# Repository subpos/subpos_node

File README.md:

# SubPos Node Gerber Files and Firmware

The latest firmware should be used with the latest version of the ESP firmware, available here - https://github.com/subpos/esp_firmware_v2

You can order 3 of these boards for $7.5 including shipping from OSHPark here - https://oshpark.com/shared_projects/0TVEe4yb

Note, the current Node design will not support Time of Flight. Because of this, there is no need to populate QG1 as the firmware just uses the internal PIC oscillator.

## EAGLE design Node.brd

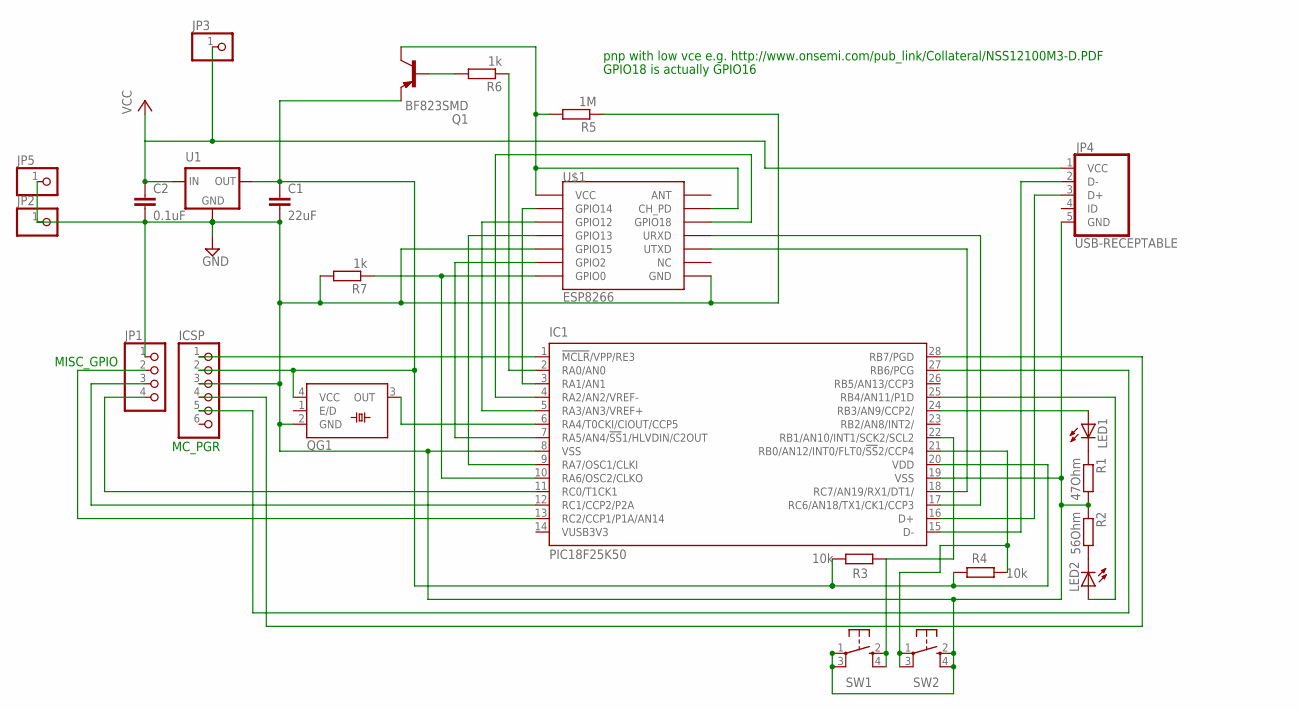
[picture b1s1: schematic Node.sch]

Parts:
C1: 22uF; C0805
C2: 0.1uF; C0805
IC1: PIC18F25K50; SO28W
ICSP: PINHD-1X6; 1X06
JP1: PINHD-1X4; 1X04
JP2, JP3, JP5: PINHD-1X1; 1X01
JP4: USB-RECEPTABLE; FCI-10103594-0001LF
LED1, LED2: LEDCHIPLED_0805; CHIPLED_0805
Q1: BF823SMD; SOT23-BEC
QG1: SM77H
R1: 47Ohm; M0805
R2: 56Ohm; M0805
R3, R4: 10k; M0805
R5: 1M; M0805
R6, R7: 1k; M0805
SW1, SW2: SPST_TACT-KMR2; KMR2
U1: MIC5209-X.XYS; SOT223
U$1: ESP8266; ESP-03

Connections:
GND: C1.2, C2.2, IC1.8 (VSS), IC1.19 (VSS), ICSP.3, JP1.1, JP2.1, JP4.5 (GND), JP5.1, QG1.2 (GND), R1.2, R2.1, R5.1, R7.2, SW1.1, SW1.3 (P1), SW2.2 (S), SW2.4 (S1), U1.2 (GND), U1.4 (GND), U$1.GND, U$1.GPIO15
unnamed: IC1.28 (RB7/PGD), ICSP.4
unnamed: C1.1, IC1.20 (VDD), ICSP.2, Q1.E, QG1.4 (VCC), R3.1, R4.2, U1.3 (OUT)
unnamed: IC1.27 (RB6/PCG), ICSP.5
unnamed: IC1.2 (RA0/AN0), R6.1
unnamed: IC1.17 (RC6/AN18/TX1/CK1/CCP3), U$1.URXD
unnamed: IC1.18 (RC7/AN19/RX1/DT1/), U$1.UTXD
unnamed: IC1.1 (!MCLR!/VPP/RE3), ICSP.1
unnamed: IC1.3 (RA1/AN1), U$1.GPIO14
unnamed: IC1.5 (RA3/AN3/VREF+), U$1.GPIO12
unnamed: IC1.16 (D+), JP4.3 (D+)
unnamed: IC1.15 (D-), JP4.2 (D-)
unnamed: LED1.C, R1.1
unnamed: IC1.24 (RB3/AN9/CCP2/), LED1.A
unnamed: LED2.C, R2.2
unnamed: IC1.25 (RB4/AN11/P1D), LED2.A
unnamed: IC1.11 (RC0/T1CK1), JP1.4
unnamed: IC1.13 (RC2/CCP1/P1A/AN14), JP1.2
unnamed: IC1.9 (RA7/OSC1/CLKI), U$1.GPIO13
unnamed: IC1.6 (RA4/T0CKI/CIOUT/CCP5), QG1.3 (OUT)
unnamed: IC1.12 (RC1/CCP2/P2A), JP1.3
unnamed: IC1.7 (RA5/AN4/!SS!1/HLVDIN/C2OUT), U$1.GPIO2
unnamed: IC1.4 (RA2/AN2/VREF-), U$1.GPIO18
unnamed: IC1.10 (RA6/OSC2/CLKO), R7.1, U$1.GPIO0
unnamed: IC1.22 (RB1/AN10/INT1/SCK2/SCL2), R3.2, SW1.2 (S), SW1.4 (S1)
unnamed: IC1.21 (RB0/AN12/INT0/FLT0/!SS!2/CCP4), R4.1, SW2.1, SW2.3 (P1)
unnamed: Q1.B, R6.2
unnamed: Q1.C, R5.2, U$1.CH_PD, U$1.VCC
VCC: C2.1, JP3.1, JP4.1 (VCC), U1.1 (IN)

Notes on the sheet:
MC_PGR
MISC_GPIO
GPIO18 is actually GPIO16
pnp with low vce e.g. http://www.onsemi.com/pub_link/Collateral/NSS12100M3-D.PDF

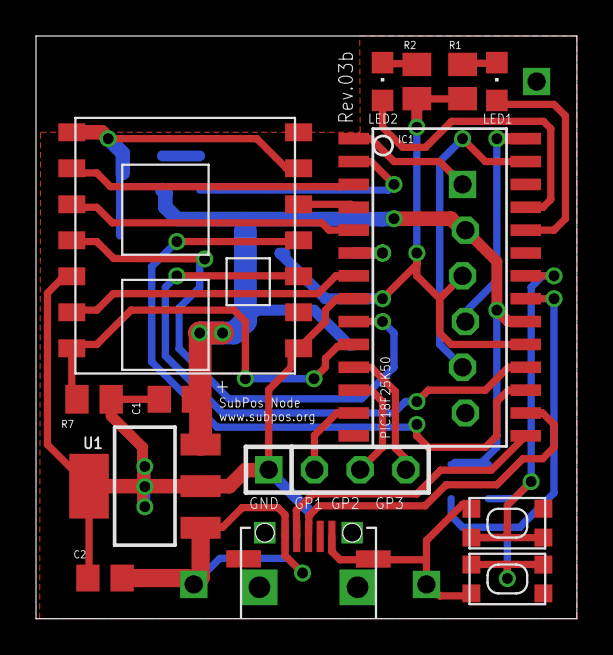
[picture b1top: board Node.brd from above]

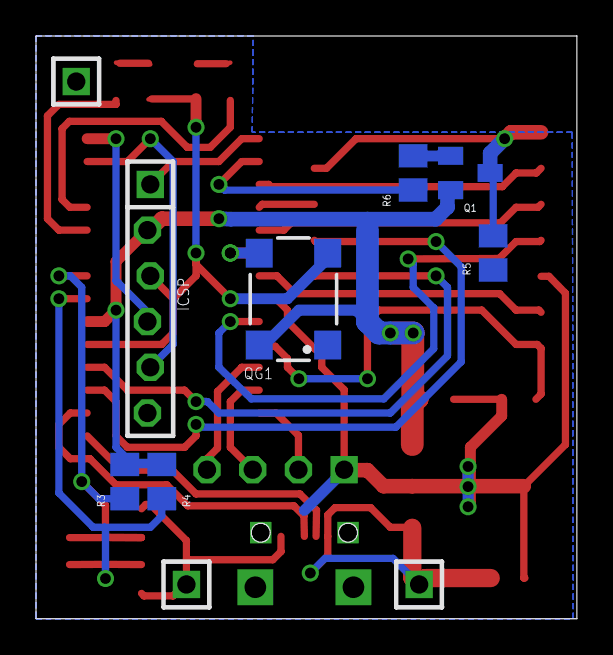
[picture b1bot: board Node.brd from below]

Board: 2 copper layers, 30.0 x 32.4 mm, 24 parts (9 on the bottom side), 29 nets.

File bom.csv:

Part;Value;Device;Package;Description
C1;22µF Tantalum 4V;C-EUC0805;C0805;CAPACITOR, European symbol
C2;0.1µF Ceramic 25V ;C-EUC0805;C0805;CAPACITOR, European symbol
IC1;PIC18F25K50;PIC18F25K50-I/SO;SO28W;PIC18F25K50 28 pin DIP
ICSP;2.54mm;PINHD-1X6;1X06;PIN HEADER
JP1;2.54mm;PINHD-1X4;1X04;PIN HEADER
JP2;;FCI-10103594-0001LF;USB-RECEPTABLE;USB Receptable
LED1;RED 22MCD;KPT-2012LSURCK;CHIPLED_0805;LED
LED2;GREEN 3MCD;KPT-2012LCGCK;CHIPLED_0805;LED
Q1;PNP Low Vce;NSV40200LT1G ;SOT23-BEC;PNP Transistror
R1;47Ohm;R-EU_M0805;M0805;RESISTOR, European symbol
R2;56Ohm;R-EU_M0805;M0805;RESISTOR, European symbol
R3;10k;R-EU_M0805;M0805;RESISTOR, European symbol
R4;10k;R-EU_M0805;M0805;RESISTOR, European symbol
R5;1M;R-EU_M0805;M0805;RESISTOR, European symbol
R6;1k;R-EU_M0805;M0805;RESISTOR, European symbol
R7;1k;R-EU_M0805;M0805;RESISTOR, European symbol
SW1;SPST_TACT-KMR2;SPST_TACT-KMR2;KMR2;SMT 6mm switch, EVQQ2 series
SW2;SPST_TACT-KMR2;SPST_TACT-KMR2;KMR2;SMT 6mm switch, EVQQ2 series
U1;MIC5209-X.XYS;MIC5209-3.3YS ;SOT223;LDO REGULATOR
U2;ESP8266;ESP8266;ESP-03;ESP8266 Wifi module 03 & 04

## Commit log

2015-09-19 SubPos Node Rev 03a PCB files initial commit.
2015-09-19 Add firmware hex.
2015-09-19 Added USB Driver
2015-09-19 Firmware now works when plugged into USB power only.
2015-09-20 Fix output buffer flushing so pastes now work to terminal.
2015-09-20 Fix issue where subpos data is retained on reset when never storing to eeprom.
2015-10-01 Fixed issues with USB ESP module flashing. Flashes now work at a slower speed (9600 Baud) as this is more reliable. You don't need to select this port speed when flashing, it will automatically do th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
2015-10-02 Added R5 to GPIO0 to pulldown. Fixed USB connector pads to add structural integrity.
2015-10-22 Fix issue when connecting to USB power supply.
2016-01-07 LICENCE
    Add Licence
2016-01-24 Updated Node firmware to work with esp_firmware_v2.
2016-01-24 Change to version date (previously incorrect).
2016-02-04 Added Eagle sources and Schematic.png
2016-02-05 Update README.md
    Add ordering information.

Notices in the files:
parts and their libraries:
micrel2: Copyright (C) 2008, Bob Starr
